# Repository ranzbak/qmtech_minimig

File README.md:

# Open Adaptive Amiga Retro System (Open AARS)

This PCB has been designed for my project in order to run the Minimig Amiga core on a board of my own design.
The core FPGA board I bought of Aliexpress, because soldering the very fine pitched BGA socket is too cumbersome.

More detailed documents regarding the I/O board can be found in the docs directory in this repository.

The board as is works, the features have been tested individually, but I'm still working on the Minimig port at this time.
Since I work on this in my spare time progress is not super fast, but progress is made.
For now I'm mostly learning and developing at the same time so a lot of stuff changes.
When the code base becomes more stable and usable I'll open the repository up.

[Firmware](https://github.com/ranzbak/MinimigAGA_TC64) for the Amiga works!

## Interfaces provided by this I/O board

- Atari/Amiga compatible Joystick ports
- PS/2 keyboard interface for mouse and keyboard
- Analog head phone jack via
- External floppy interface to connect Amiga floppy drives (Including 12V power pin)
- HDMI display connector that supports up to full HD video (1920x1080)
- 6 status LEDS
- Internal Amiga floppy drive connector
- External Amiga floppy drive connector (DIN-23)
- AS4C16M16SA-6TCN 32Mb SDRAM
- ADV7511 HDMI output PHY
- MAX9850 I2S Audio chip with built in amplifier
- SD-card interface
- RS-232 over USB to program and communicate with the Python shell

## Platforms that _could_ run with this IO board

- C64
- Amiga 1200/500(+) [https://github.com/ranzbak/MinimigAGA_TC64](https://github.com/ranzbak/MinimigAGA_TC64)
- Atari ST
- Other 80's and 90's machines?

Keep in mind I'm only planning on making an Amiga core for this board, but feel free to contribute other cores.

# The two boards that are compatible with this design are

## QM_XC7A100T_DDR3

### Specs

- On-Board FPGA: XC7A100T-2FGG676I;
- On-Board FPGA external crystal frequency: 50MHz;
- XC7A100T-2FGG676I has rich block RAM resource up to 4,860Kb;
- XC7A100T-2FGG676I has 101,440 logic cells;
- On-Board MT25QL128 SPI Flash,16M bytes for user configuration code;
- On-Board 256MB Micron DDR3，MT41K128M16JT-125:K;
- On-Board 3.3V power supply for FPGA by using MP2315 wide input range DC/DC;
- XC7A100T core board has two 64p, 2.54mm pitch headers for extending user IOs. All IOs are precisely designed with length matching;
- XC7A100T core board has 3 user switches;
- XC7A100T core board has 4 user LEDs;
- XC7A100T core board has JTAG interface, by using 6p, 2.54mm pitch header;
- XC7A100T core board PCB size is: 6.7cm x 8.4cm;
- Default power source for board is: 1A@5V DC, the DC header type: DC-050, 5.5mmx2.1mm;

### Github repo

[QM_XC7A100T_STARTER_KIT](https://github.com/ChinaQMTECH/QM_XC7A100T_STARTER_KIT)

### Listings at this time (2019-12-29)

- [Ebay QMTECH Xilinx FPGA Artix7 Artix-7 XC7A100T Core Board](https://www.ebay.com/itm/QMTECH-Xilinx-FPGA-Artix7-Artix-7-XC7A100T-Core-Board-/173922141347)
- [Aliexpress QMTECH Xilinx FPGA Artix7 Artix-7 XC7A100T DDR3 Core Board](vid=bcf629d3-8718-47b9-bad6-a31d7b1e778c&algo_expid=bcf629d3-8718-47b9-bad6-a31d7b1e778c-14&btsid=29203478-817f-4791-b6b6-1687369426ed&ws_ab_test=searchweb0_0,searchweb201602_3,searchweb201603_53)

## QM_XC7A35T_DDR3

### Specs

- On-Board FPGA: XC7A35T-1FTG256C;
- On-Board FPGA external crystal frequency: 50MHz;
- XC7A35T-1FTG256C has rich block RAM resource up to 1,800Kb;
- XC7A35T-1FTG256C has 33,280 logic cells;
- On-Board MT28QL128 SPI Flash, 16M bytes for user configuration code;
- On-Board 256MB Micron DDR3, MT41J128M16JT-125:K;
- On-Board 3.3V power supply for FPGA by using MP2315 wide input range DC/DC;
- XC7A35T development board has two 64p, 2.54mm pitch headers for extending user IOs. All IOs are precisely designed with length matching;
- XC7A35T development board has 2 user switches;
- XC7A35T development board has 3 user LEDs;
- XC7A35T development board has JTAG interface, by using 6p, 2.54mm pitch header;
- XC7A35T development board PCB size is: 6.7cm x 8.4cm;
- Default power source for board is: 1A@5V DC, the DC header type: DC-050, 5.5mmx2.1mm;

### Github repo

[QM_XC7A35T_DDR3](https://github.com/ChinaQMTECH/QM_XC7A35T_DDR3)

### Listings at this time (2019-12-29)

- [Ebay Xilinx FPGA Artix7 Artix-7 Core Board XC7A35T DDR3 256MB](https://www.ebay.com/itm/Xilinx-FPGA-Artix7-Artix-7-Core-Board-XC7A35T-DDR3-256MB/293211934785?hash=item4444cb1041:g:YGgAAOSw5SNdbdkY)
- [Aliexpress QMTECH Xilinx FPGA Artix7 Artix-7 Core Board XC7A35T DDR3 256MB](https://www.aliexpress.com/item/1000006630084.html?spm=a2g0o.productlist.0.0.41cd3b52ViiSyG&algo_pvid=42b95d99-f036-43b5-8cb0-6ca9003178e8&algo_expid=42b95d99-f036-43b5-8cb0-6ca9003178e8-3&btsid=62811540-f61c-4c9d-b4b2-447e53cca01b&ws_ab_test=searchweb0_0,searchweb201602_3,searchweb201603_53)

** Make sure to ask the seller to ship the board without the female headers soldered on, for the Open AARS board male headers are needed. **

## Disclaimer

THE PROJECT IS PROVIDED "AS IS", WITHOUT WARRANTY OF ANY KIND, EXPRESS OR IMPLIED, INCLUDING BUT NOT LIMITED TO THE WARRANTIES OF MERCHANTABILITY, FITNESS FOR A PARTICULAR PURPOSE AND NONINFRINGEMENT. IN NO EVENT SHALL THE AUTHORS OR COPYRIGHT HOLDERS BE LIABLE FOR ANY CLAIM, DAMAGES OR OTHER LIABILITY, WHETHER IN AN ACTION OF CONTRACT, TORT OR OTHERWISE, ARISING FROM, OUT OF OR IN CONNECTION WITH THE PROJECT OR THE USE OR OTHER DEALINGS IN THE PROJECT.

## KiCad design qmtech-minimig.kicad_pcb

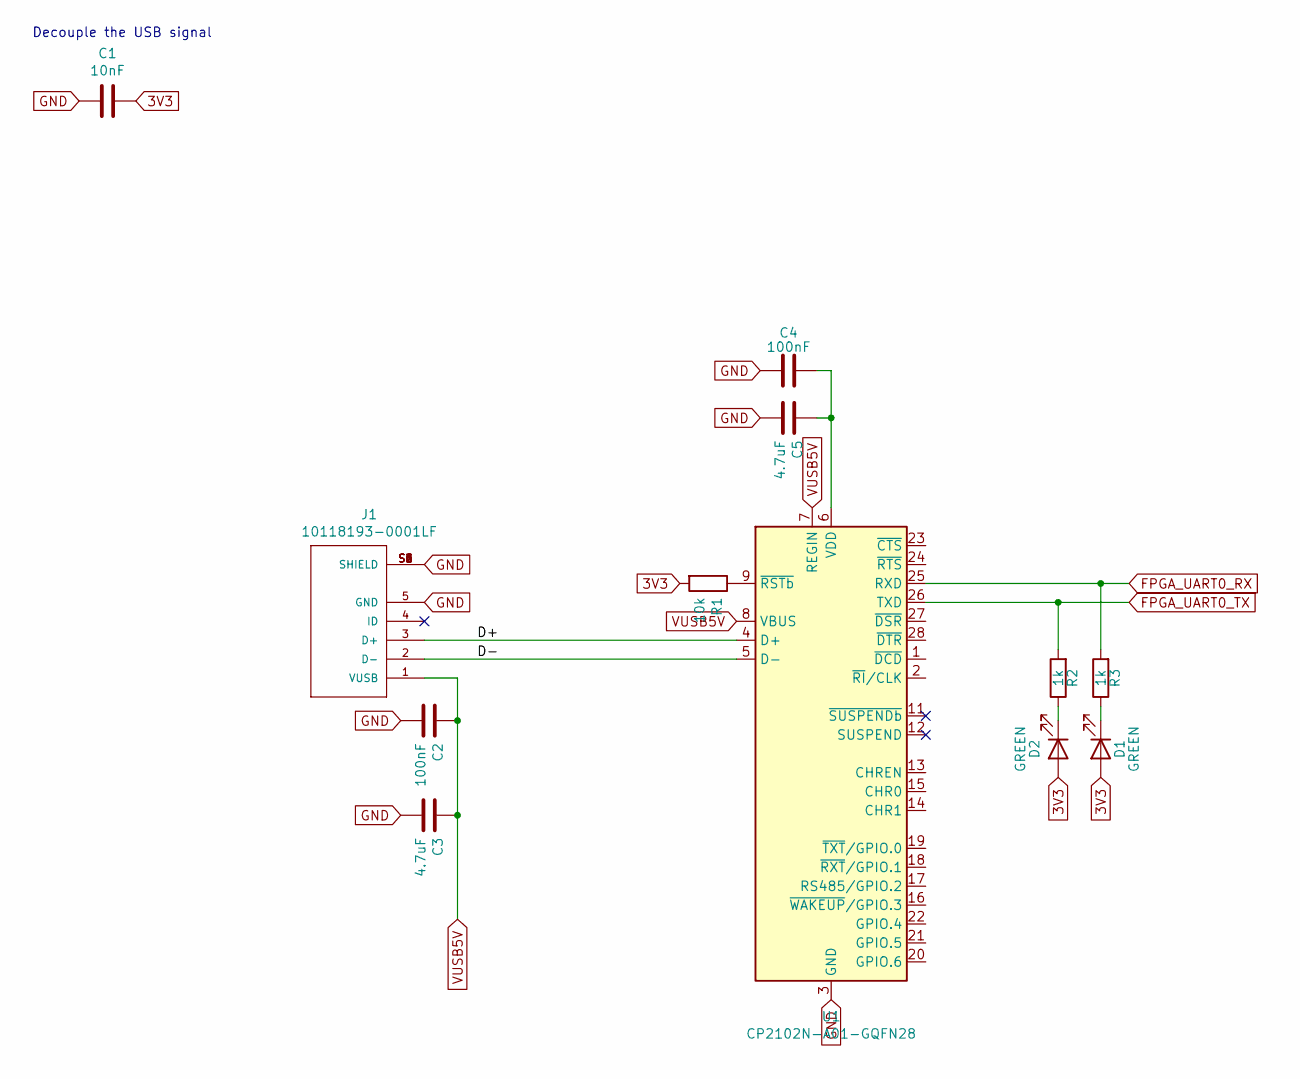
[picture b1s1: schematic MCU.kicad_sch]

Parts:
C1: 10nF; C_0603_1608Metric
C2, C4: 100nF; C_0603_1608Metric
C3, C5: 4.7uF; C_0805_2012Metric
D1, D2: GREEN; LED_0603_1608Metric
J1: 10118193-0001LF; FCI_10118193-0001LF
R1: 10k; R_0603_1608Metric
R2, R3: 1k; R_0603_1608Metric
U1: CP2102N-A01-GQFN28; QFN-28-1EP_5x5mm_P0.5mm_EP3.35x3.35mm

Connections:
3V3: C1.1, D1.2 (A), D2.2 (A), R1.2; also elsewhere on the board
/MCU/D+: J1.3 (D+), U1.4 (D+)
/MCU/D-: J1.2 (D-), U1.5 (D-)
FPGA_UART0_RX: R3.2, U1.25 (RXD); also elsewhere on the board
FPGA_UART0_TX: R2.2, U1.26 (TXD); also elsewhere on the board
unnamed: C4.2, C5.1, U1.6 (VDD)
unnamed: D1.1 (K), R2.1
unnamed: D2.1 (K), R3.1
unnamed: R1.1, U1.9 (~RSTb)
VUSB5V: C2.1, C3.1, J1.1 (VUSB), U1.7 (REGIN), U1.8 (VBUS)

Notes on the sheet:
Decouple the USB signal

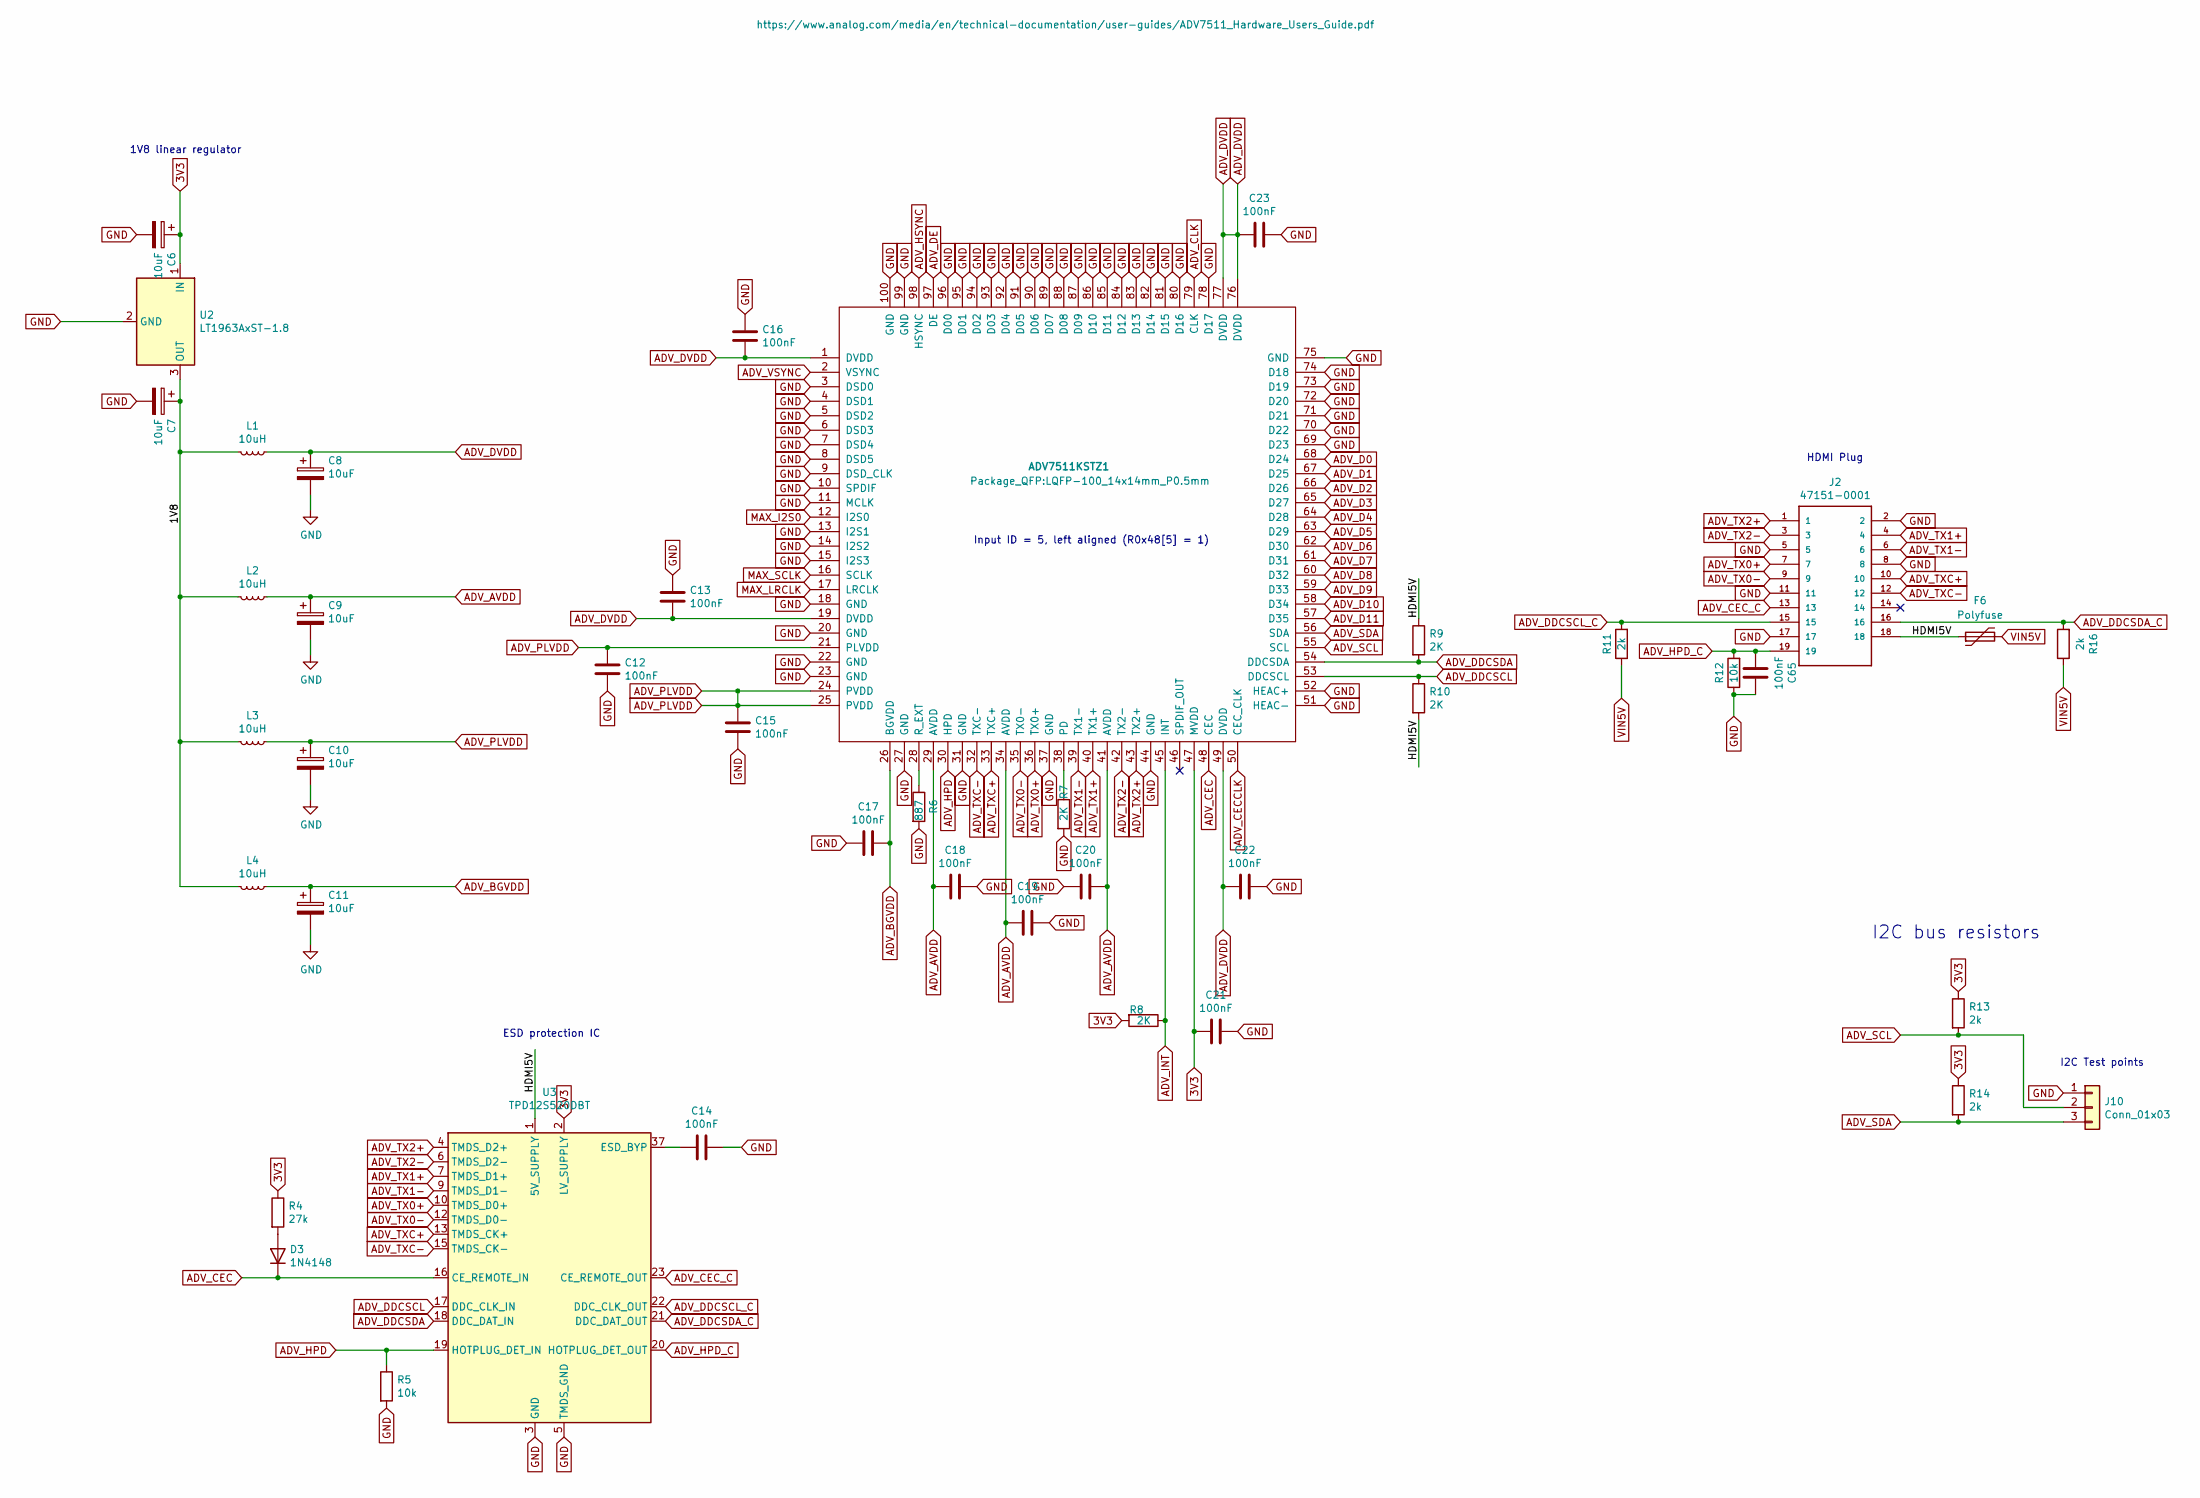
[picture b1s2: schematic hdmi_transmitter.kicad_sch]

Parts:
ADV7511KSTZ1: adv7511kstz; LQFP-100_14x14mm_P0.5mm
C6, C7, C8, C9, C10, C11: 10uF; C_0805_2012Metric
C12, C13, C14, C15, C16, C17, C18, C19, C20, C21, C22, C23, C65: 100nF; C_0603_1608Metric
D3: 1N4148; D_SOD-323
F6: Polyfuse; Fuse_0805_2012Metric
J2: 47151-0001
J10: Conn_01x03; PinHeader_1x03_P2.54mm_Vertical
L1, L2, L3, L4: 10uH; L_0805_2012Metric
R4: 27k; R_0603_1608Metric
R5, R12: 10k; R_0603_1608Metric
R6: 887; R_0603_1608Metric
R7, R8, R9, R10: 2K; R_0603_1608Metric
R11, R13, R14, R16: 2k; R_0603_1608Metric
U2: LT1963AxST-1.8; SOT-223-3_TabPin2
U3: TPD12S520DBT; TSSOP-38_4.4x9.7mm_P0.5mm

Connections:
3V3: ADV7511KSTZ1.47 (MVDD), C6.1, C21.2, R4.1, R8.2, R13.1, R14.1, U2.1 (IN), U3.2 (LV_SUPPLY); also elsewhere on the board
/HDMI transmitter/1V8: C7.1, L1.2, L2.2, L3.2, L4.2, U2.3 (OUT)
ADV_AVDD: ADV7511KSTZ1.29 (AVDD), ADV7511KSTZ1.34 (AVDD), ADV7511KSTZ1.41 (AVDD), C9.1, C18.2, C19.2, C20.1, L2.1
ADV_BGVDD: ADV7511KSTZ1.26 (BGVDD), C11.1, C17.1, L4.1
ADV_CEC: ADV7511KSTZ1.48 (CEC), D3.1 (K), U3.16 (CE_REMOTE_IN)
ADV_CECCLK: ADV7511KSTZ1.50 (CEC_CLK); also elsewhere on the board
ADV_CEC_C: J2.13, U3.23 (CE_REMOTE_OUT)
ADV_CLK: ADV7511KSTZ1.79 (CLK); also elsewhere on the board
ADV_D0: ADV7511KSTZ1.68 (D24); also elsewhere on the board
ADV_D1: ADV7511KSTZ1.67 (D25); also elsewhere on the board
ADV_D2: ADV7511KSTZ1.66 (D26); also elsewhere on the board
ADV_D3: ADV7511KSTZ1.65 (D27); also elsewhere on the board
ADV_D4: ADV7511KSTZ1.64 (D28); also elsewhere on the board
ADV_D5: ADV7511KSTZ1.63 (D29); also elsewhere on the board
ADV_D6: ADV7511KSTZ1.62 (D30); also elsewhere on the board
ADV_D7: ADV7511KSTZ1.61 (D31); also elsewhere on the board
ADV_D8: ADV7511KSTZ1.60 (D32); also elsewhere on the board
ADV_D9: ADV7511KSTZ1.59 (D33); also elsewhere on the board
ADV_D10: ADV7511KSTZ1.58 (D34); also elsewhere on the board
ADV_D11: ADV7511KSTZ1.57 (D35); also elsewhere on the board
ADV_DDCSCL: ADV7511KSTZ1.53 (DDCSCL), R10.1, U3.17 (DDC_CLK_IN)
ADV_DDCSCL_C: J2.15, R11.2, U3.22 (DDC_CLK_OUT)
ADV_DDCSDA: ADV7511KSTZ1.54 (DDCSDA), R9.2, U3.18 (DDC_DAT_IN)
ADV_DDCSDA_C: J2.16, R16.2, U3.21 (DDC_DAT_OUT)
ADV_DE: ADV7511KSTZ1.97 (DE); also elsewhere on the board
ADV_DVDD: ADV7511KSTZ1.1 (DVDD), ADV7511KSTZ1.19 (DVDD), ADV7511KSTZ1.49 (DVDD), ADV7511KSTZ1.76 (DVDD), ADV7511KSTZ1.77 (DVDD), C8.1, C13.1, C16.1, C22.2, C23.2, L1.1
ADV_HPD: ADV7511KSTZ1.30 (HPD), R5.1, U3.19 (HOTPLUG_DET_IN)
ADV_HPD_C: C65.2, J2.19, R12.2, U3.20 (HOTPLUG_DET_OUT)
ADV_HSYNC: ADV7511KSTZ1.98 (HSYNC); also elsewhere on the board
ADV_INT: ADV7511KSTZ1.45 (INT), R8.1; also elsewhere on the board
ADV_PLVDD: ADV7511KSTZ1.21 (PLVDD), ADV7511KSTZ1.24 (PVDD), ADV7511KSTZ1.25 (PVDD), C10.1, C12.2, C15.2, L3.1
ADV_SCL: ADV7511KSTZ1.55 (SCL), J10.2, R13.2; also elsewhere on the board
ADV_SDA: ADV7511KSTZ1.56 (SDA), J10.3, R14.2; also elsewhere on the board
ADV_TX0+: ADV7511KSTZ1.36 (TX0+), J2.7, U3.10 (TMDS_D0+), U3.29 (TMDS_D0+)
ADV_TX0-: ADV7511KSTZ1.35 (TX0-), J2.9, U3.12 (TMDS_D0-), U3.27 (TMDS_D0-)
ADV_TX1+: ADV7511KSTZ1.40 (TX1+), J2.4, U3.7 (TMDS_D1+), U3.32 (TMDS_D1+)
ADV_TX1-: ADV7511KSTZ1.39 (TX1-), J2.6, U3.9 (TMDS_D1-), U3.30 (TMDS_D1-)
ADV_TX2+: ADV7511KSTZ1.43 (TX2+), J2.1, U3.4 (TMDS_D2+), U3.35 (TMDS_D2+)
ADV_TX2-: ADV7511KSTZ1.42 (TX2-), J2.3, U3.6 (TMDS_D2-), U3.33 (TMDS_D2-)
ADV_TXC+: ADV7511KSTZ1.33 (TXC+), J2.10, U3.13 (TMDS_CK+), U3.26 (TMDS_CK+)
ADV_TXC-: ADV7511KSTZ1.32 (TXC-), J2.12, U3.15 (TMDS_CK-), U3.24 (TMDS_CK-)
ADV_VSYNC: ADV7511KSTZ1.2 (VSYNC); also elsewhere on the board
MAX_I2S0: ADV7511KSTZ1.12 (I2S0); also elsewhere on the board
MAX_LRCLK: ADV7511KSTZ1.17 (LRCLK); also elsewhere on the board
MAX_SCLK: ADV7511KSTZ1.16 (SCLK); also elsewhere on the board
unnamed: ADV7511KSTZ1.28 (R_EXT), R6.1
unnamed: ADV7511KSTZ1.38 (PD), R7.1
unnamed: C14.2, U3.37 (ESD_BYP)
unnamed: D3.2 (A), R4.2

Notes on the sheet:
1V8 linear regulator
HDMI Plug
Input ID = 5, left aligned (R0x48[5] = 1)
ESD protection IC
I2C Test points
I2C bus resistors

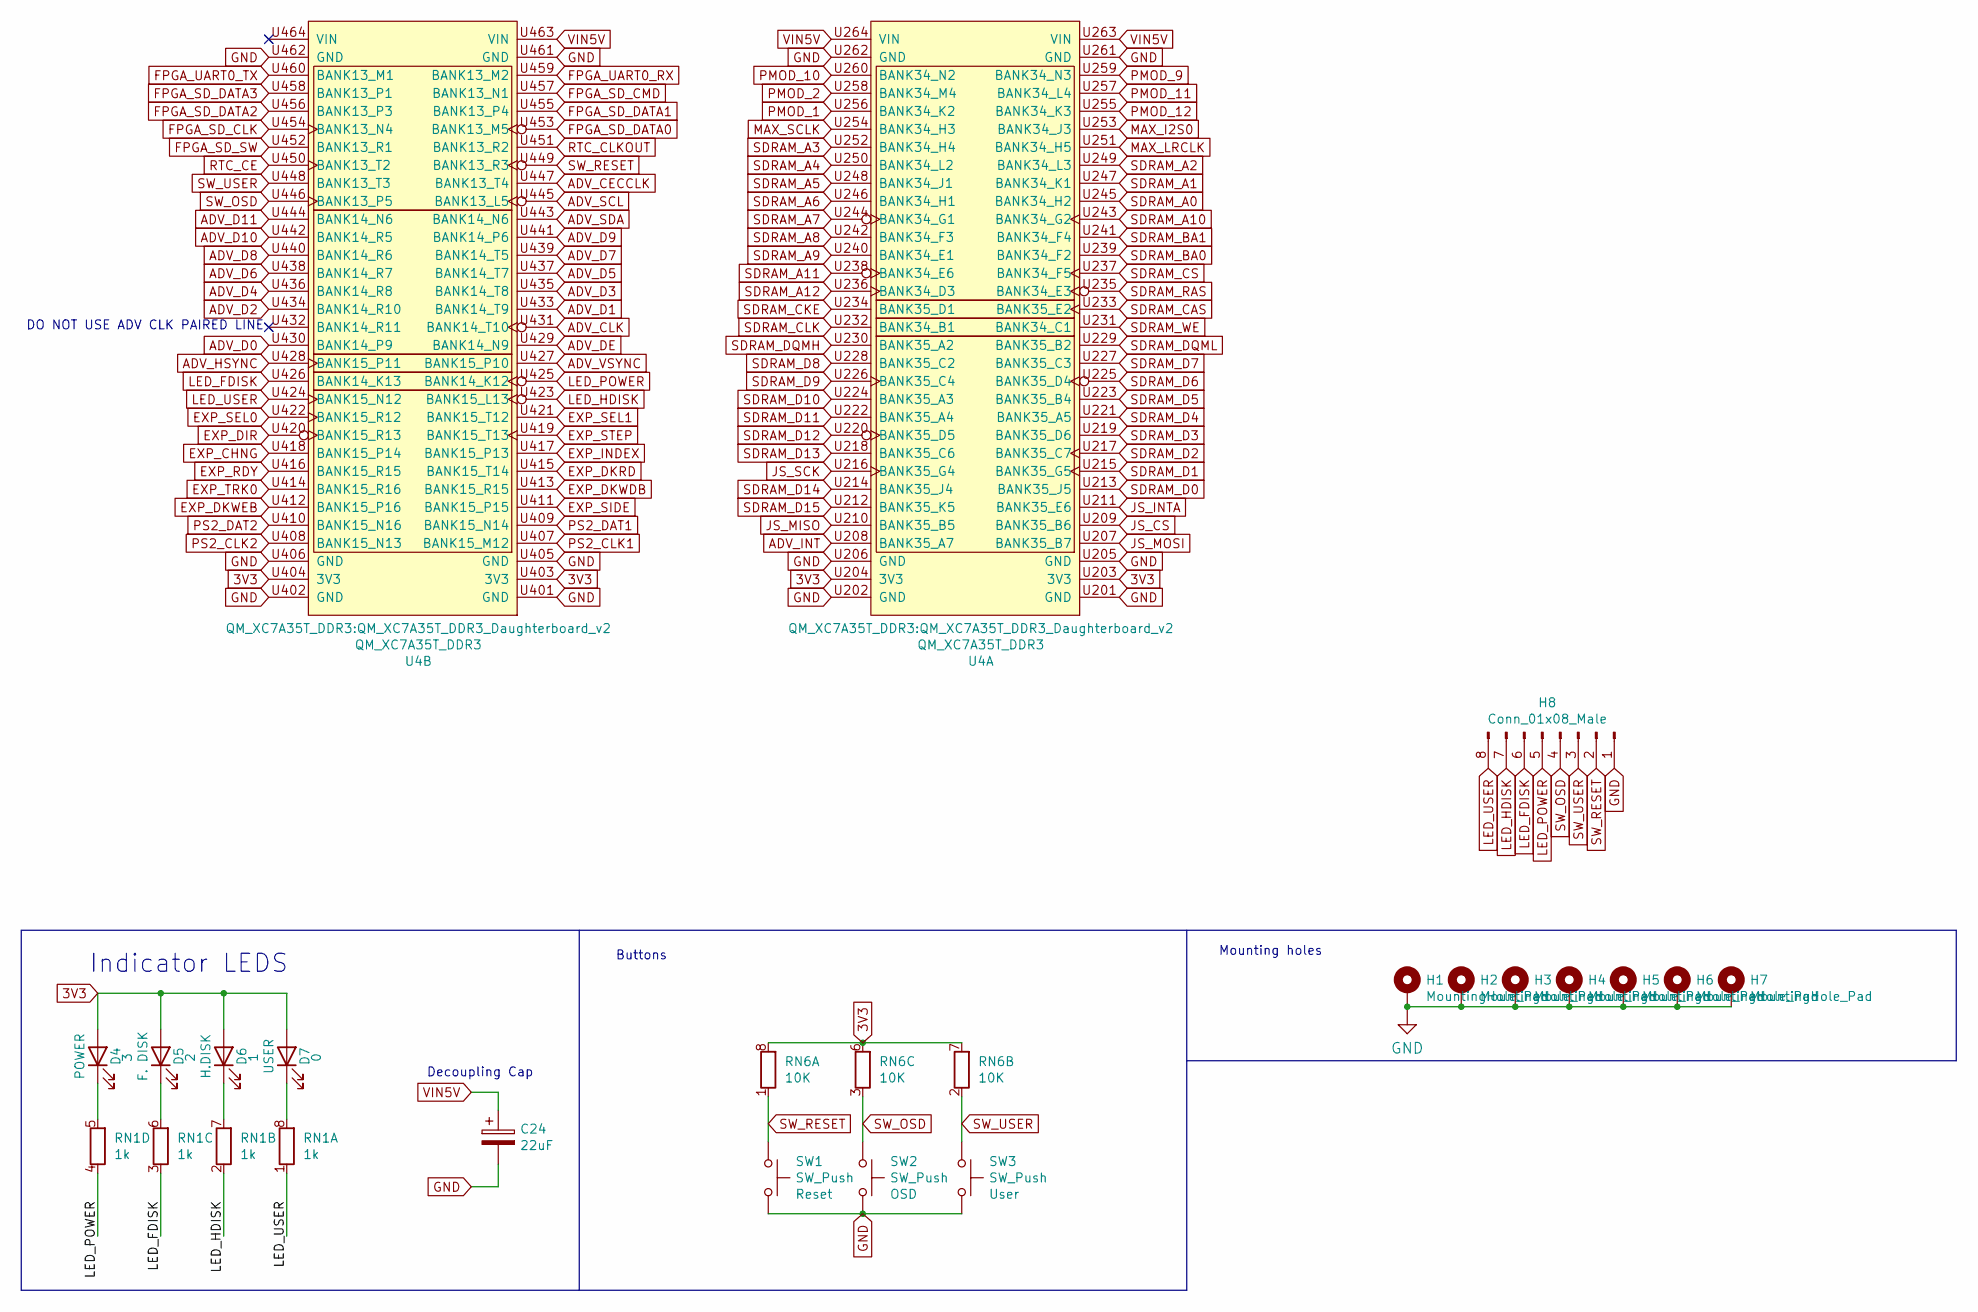
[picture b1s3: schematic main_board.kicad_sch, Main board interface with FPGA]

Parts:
C24: 22uF; CP_Elec_5x5.4
D4: 3; LED_0603_1608Metric
D5: 2; LED_0603_1608Metric
D6: 1; LED_0603_1608Metric
D7: 0; LED_0603_1608Metric
H1, H2, H3, H4, H5, H6, H7: MountingHole_Pad; MountingHole_3.2mm_M3_DIN965_Pad
H8: Conn_01x08_Male; PinHeader_1x08_P2.54mm_Vertical
RN1: 1k; R_Array_Convex_4x0603
RN6: 10K; R_Array_Concave_4x0603
SW1, SW2, SW3: SW_Push; SW_SPST_EVQQ2
U4: QM_XC7A35T_DDR3; QM_XC7A35T_DDR3_Daughterboard_v2

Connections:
3V3: D4.2 (A), D5.2 (A), D6.2 (A), D7.2 (A), RN6.6 (R3.2), RN6.7 (R2.2), RN6.8 (R1.2), U4.U203 (3V3), U4.U204 (3V3), U4.U403 (3V3), U4.U404 (3V3); also elsewhere on the board
ADV_CECCLK: U4.U447 (BANK13_T4); also elsewhere on the board
ADV_CLK: U4.U431 (BANK14_T10); also elsewhere on the board
ADV_D0: U4.U430 (BANK14_P9); also elsewhere on the board
ADV_D1: U4.U433 (BANK14_T9); also elsewhere on the board
ADV_D2: U4.U434 (BANK14_R10); also elsewhere on the board
ADV_D3: U4.U435 (BANK14_T8); also elsewhere on the board
ADV_D4: U4.U436 (BANK14_R8); also elsewhere on the board
ADV_D5: U4.U437 (BANK14_T7); also elsewhere on the board
ADV_D6: U4.U438 (BANK14_R7); also elsewhere on the board
ADV_D7: U4.U439 (BANK14_T5); also elsewhere on the board
ADV_D8: U4.U440 (BANK14_R6); also elsewhere on the board
ADV_D9: U4.U441 (BANK14_P6); also elsewhere on the board
ADV_D10: U4.U442 (BANK14_R5); also elsewhere on the board
ADV_D11: U4.U444 (BANK14_N6); also elsewhere on the board
ADV_DE: U4.U429 (BANK14_N9); also elsewhere on the board
ADV_HSYNC: U4.U428 (BANK15_P11); also elsewhere on the board
ADV_INT: U4.U208 (BANK35_A7); also elsewhere on the board
ADV_SCL: U4.U445 (BANK13_L5); also elsewhere on the board
ADV_SDA: U4.U443 (BANK14_N6); also elsewhere on the board
ADV_VSYNC: U4.U427 (BANK15_P10); also elsewhere on the board
EXP_CHNG: U4.U418 (BANK15_P14); also elsewhere on the board
EXP_DIR: U4.U420 (BANK15_R13); also elsewhere on the board
EXP_DKRD: U4.U415 (BANK15_T14); also elsewhere on the board
EXP_DKWDB: U4.U413 (BANK15_R15); also elsewhere on the board
EXP_DKWEB: U4.U412 (BANK15_P16); also elsewhere on the board
EXP_INDEX: U4.U417 (BANK15_P13); also elsewhere on the board
EXP_RDY: U4.U416 (BANK15_R15); also elsewhere on the board
EXP_SEL0: U4.U422 (BANK15_R12); also elsewhere on the board
EXP_SEL1: U4.U421 (BANK15_T12); also elsewhere on the board
EXP_SIDE: U4.U411 (BANK15_P15); also elsewhere on the board
EXP_STEP: U4.U419 (BANK15_T13); also elsewhere on the board
EXP_TRK0: U4.U414 (BANK15_R16); also elsewhere on the board
FPGA_SD_CLK: U4.U454 (BANK13_N4); also elsewhere on the board
FPGA_SD_CMD: U4.U457 (BANK13_N1); also elsewhere on the board
FPGA_SD_DATA0: U4.U453 (BANK13_M5); also elsewhere on the board
FPGA_SD_DATA1: U4.U455 (BANK13_P4); also elsewhere on the board
FPGA_SD_DATA2: U4.U456 (BANK13_P3); also elsewhere on the board
FPGA_SD_DATA3: U4.U458 (BANK13_P1); also elsewhere on the board
FPGA_UART0_RX: U4.U459 (BANK13_M2); also elsewhere on the board
FPGA_UART0_TX: U4.U460 (BANK13_M1); also elsewhere on the board
JS_CS: U4.U209 (BANK35_B6); also elsewhere on the board
JS_INTA: U4.U211 (BANK35_E6); also elsewhere on the board
JS_MISO: U4.U210 (BANK35_B5); also elsewhere on the board
JS_MOSI: U4.U207 (BANK35_B7); also elsewhere on the board
JS_SCK: U4.U216 (BANK35_G4); also elsewhere on the board
LED_FDISK: H8.6, RN1.3 (R3.1), U4.U426 (BANK14_K13)
LED_HDISK: H8.7, RN1.2 (R2.1), U4.U423 (BANK15_L13)
LED_POWER: H8.5, RN1.4 (R4.1), U4.U425 (BANK14_K12)
LED_USER: H8.8, RN1.1 (R1.1), U4.U424 (BANK15_N12)
MAX_I2S0: U4.U253 (BANK34_J3); also elsewhere on the board
MAX_LRCLK: U4.U251 (BANK34_H5); also elsewhere on the board
MAX_SCLK: U4.U254 (BANK34_H3); also elsewhere on the board
unnamed: D4.1 (K), RN1.5 (R4.2)
unnamed: D5.1 (K), RN1.6 (R3.2)
unnamed: D6.1 (K), RN1.7 (R2.2)
unnamed: D7.1 (K), RN1.8 (R1.2)
PMOD_1: U4.U256 (BANK34_K2); also elsewhere on the board
PMOD_2: U4.U258 (BANK34_M4); also elsewhere on the board
PMOD_9: U4.U259 (BANK34_N3); also elsewhere on the board
PMOD_10: U4.U260 (BANK34_N2); also elsewhere on the board
PMOD_11: U4.U257 (BANK34_L4); also elsewhere on the board
PMOD_12: U4.U255 (BANK34_K3); also elsewhere on the board
PS2_CLK1: U4.U407 (BANK15_M12); also elsewhere on the board
PS2_CLK2: U4.U408 (BANK15_N13); also elsewhere on the board
PS2_DAT1: U4.U409 (BANK15_N14); also elsewhere on the board
PS2_DAT2: U4.U410 (BANK15_N16); also elsewhere on the board
SDRAM_A0: U4.U245 (BANK34_H2); also elsewhere on the board
SDRAM_A1: U4.U247 (BANK34_K1); also elsewhere on the board
SDRAM_A2: U4.U249 (BANK34_L3); also elsewhere on the board
SDRAM_A3: U4.U252 (BANK34_H4); also elsewhere on the board
SDRAM_A4: U4.U250 (BANK34_L2); also elsewhere on the board
SDRAM_A5: U4.U248 (BANK34_J1); also elsewhere on the board
SDRAM_A6: U4.U246 (BANK34_H1); also elsewhere on the board
SDRAM_A7: U4.U244 (BANK34_G1); also elsewhere on the board
SDRAM_A8: U4.U242 (BANK34_F3); also elsewhere on the board
SDRAM_A9: U4.U240 (BANK34_E1); also elsewhere on the board
SDRAM_A10: U4.U243 (BANK34_G2); also elsewhere on the board
SDRAM_A11: U4.U238 (BANK34_E6); also elsewhere on the board
SDRAM_A12: U4.U236 (BANK34_D3); also elsewhere on the board
SDRAM_BA0: U4.U239 (BANK34_F2); also elsewhere on the board
SDRAM_BA1: U4.U241 (BANK34_F4); also elsewhere on the board
SDRAM_CAS: U4.U233 (BANK35_E2); also elsewhere on the board
SDRAM_CKE: U4.U234 (BANK35_D1); also elsewhere on the board
SDRAM_CLK: U4.U232 (BANK34_B1); also elsewhere on the board
SDRAM_CS: U4.U237 (BANK34_F5); also elsewhere on the board
SDRAM_D0: U4.U213 (BANK35_J5); also elsewhere on the board
SDRAM_D1: U4.U215 (BANK35_G5); also elsewhere on the board
SDRAM_D2: U4.U217 (BANK35_C7); also elsewhere on the board
SDRAM_D3: U4.U219 (BANK35_D6); also elsewhere on the board
SDRAM_D4: U4.U221 (BANK35_A5); also elsewhere on the board
SDRAM_D5: U4.U223 (BANK35_B4); also elsewhere on the board
SDRAM_D6: U4.U225 (BANK35_D4); also elsewhere on the board
SDRAM_D7: U4.U227 (BANK35_C3); also elsewhere on the board
SDRAM_D8: U4.U228 (BANK35_C2); also elsewhere on the board
SDRAM_D9: U4.U226 (BANK35_C4); also elsewhere on the board
SDRAM_D10: U4.U224 (BANK35_A3); also elsewhere on the board
SDRAM_D11: U4.U222 (BANK35_A4); also elsewhere on the board
SDRAM_D12: U4.U220 (BANK35_D5); also elsewhere on the board
SDRAM_D13: U4.U218 (BANK35_C6); also elsewhere on the board
SDRAM_D14: U4.U214 (BANK35_J4); also elsewhere on the board
SDRAM_D15: U4.U212 (BANK35_K5); also elsewhere on the board
SDRAM_DQMH: U4.U230 (BANK35_A2); also elsewhere on the board
SDRAM_DQML: U4.U229 (BANK35_B2); also elsewhere on the board
SDRAM_RAS: U4.U235 (BANK34_E3); also elsewhere on the board
SDRAM_WE: U4.U231 (BANK34_C1); also elsewhere on the board
VIN5V: C24.1, U4.U263 (VIN), U4.U264 (VIN), U4.U463 (VIN); also elsewhere on the board

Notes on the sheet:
DO NOT USE ADV CLK PAIRED LINE
Buttons
Decoupling Cap
Mounting holes
Indicator LEDS

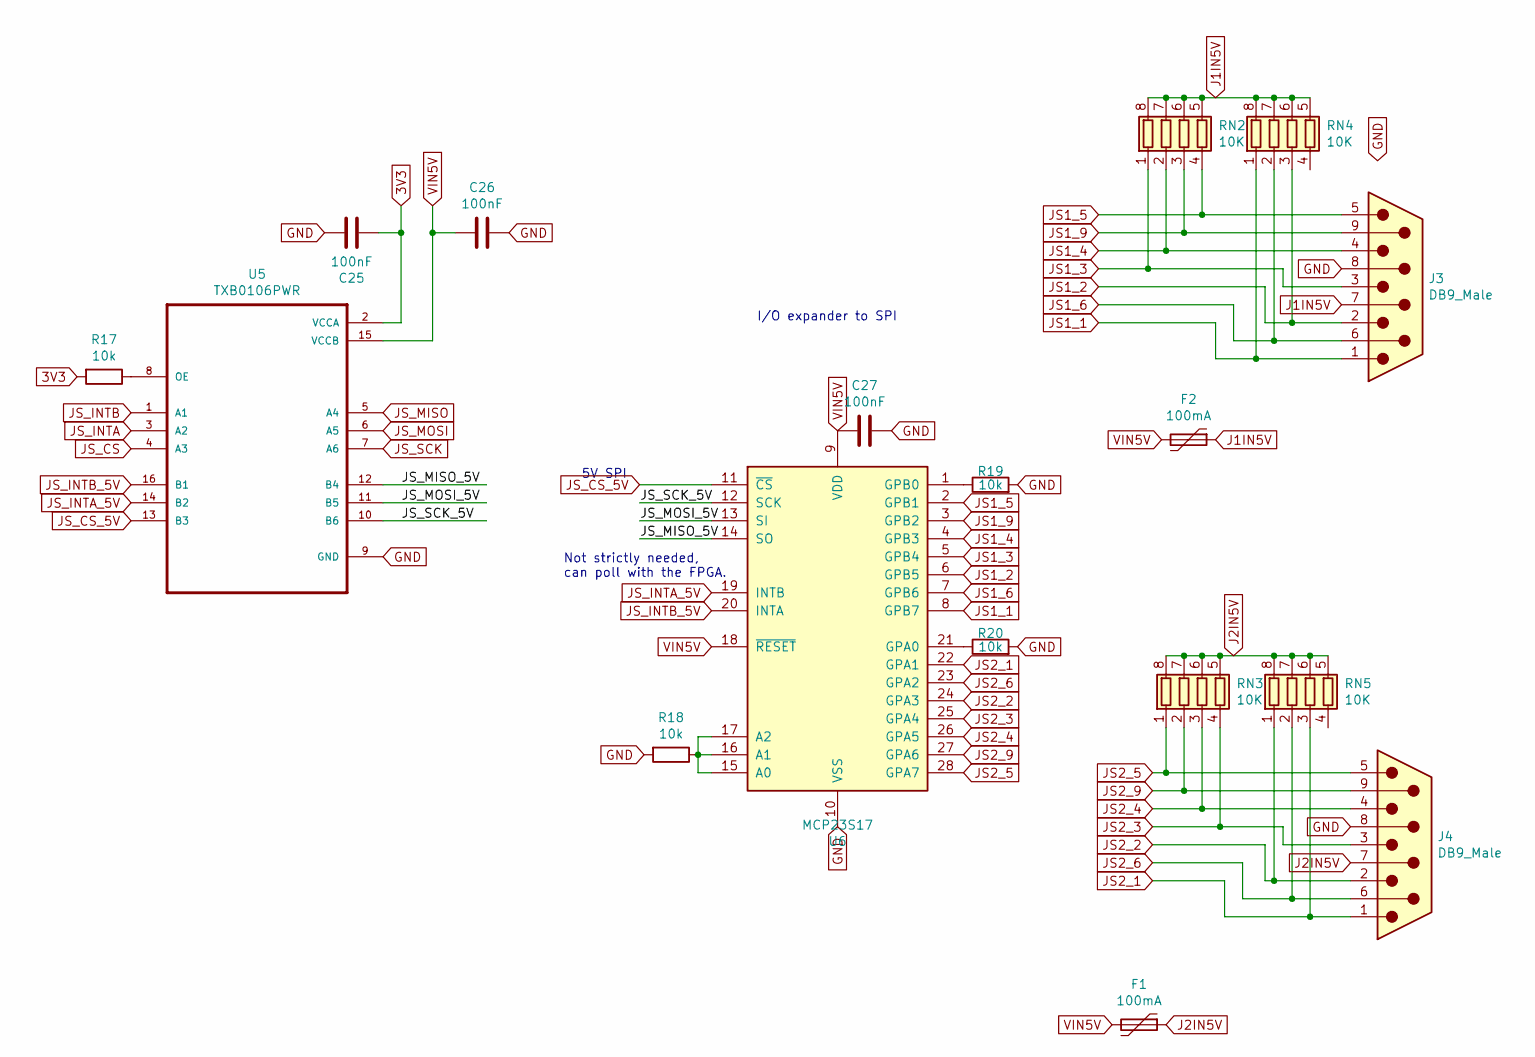
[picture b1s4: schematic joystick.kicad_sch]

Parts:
C25, C26, C27: 100nF; C_0603_1608Metric
F1, F2: 100mA; Fuse_0805_2012Metric
J3, J4: DB9_Male; DSUB-9_Male_Horizontal_P2.77x2.84mm_EdgePinOffset7.70mm_Hou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
R17, R18, R19, R20: 10k; R_0603_1608Metric
RN2, RN3, RN4, RN5: 10K; R_Array_Convex_4x0603
U5: TXB0106PWR; SOP65P640X120-16N
U6: MCP23S17; SSOP-28_5.3x10.2mm_P0.65mm

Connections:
3V3: C25.2, R17.2, U5.2 (VCCA); also elsewhere on the board
/Joystick/JS_MISO_5V: U5.12 (B4), U6.14 (SO)
/Joystick/JS_MOSI_5V: U5.11 (B5), U6.13 (SI)
/Joystick/JS_SCK_5V: U5.10 (B6), U6.12 (SCK)
J1IN5V: F2.1, J3.7, RN2.5 (R4.2), RN2.6 (R3.2), RN2.7 (R2.2), RN2.8 (R1.2), RN4.5 (R4.2), RN4.6 (R3.2), RN4.7 (R2.2), RN4.8 (R1.2)
J2IN5V: F1.1, J4.7, RN3.5 (R4.2), RN3.6 (R3.2), RN3.7 (R2.2), RN3.8 (R1.2), RN5.5 (R4.2), RN5.6 (R3.2), RN5.7 (R2.2), RN5.8 (R1.2)
JS1_1: J3.1, RN4.1 (R1.1), U6.8 (GPB7)
JS1_2: J3.2, RN4.3 (R3.1), U6.6 (GPB5)
JS1_3: J3.3, RN2.1 (R1.1), U6.5 (GPB4)
JS1_4: J3.4, RN2.2 (R2.1), U6.4 (GPB3)
JS1_5: J3.5, RN2.4 (R4.1), U6.2 (GPB1)
JS1_6: J3.6, RN4.2 (R2.1), U6.7 (GPB6)
JS1_9: J3.9, RN2.3 (R3.1), U6.3 (GPB2)
JS2_1: J4.1, RN5.3 (R3.1), U6.22 (GPA1)
JS2_2: J4.2, RN5.1 (R1.1), U6.24 (GPA3)
JS2_3: J4.3, RN3.4 (R4.1), U6.25 (GPA4)
JS2_4: J4.4, RN3.3 (R3.1), U6.26 (GPA5)
JS2_5: J4.5, RN3.1 (R1.1), U6.28 (GPA7)
JS2_6: J4.6, RN5.2 (R2.1), U6.23 (GPA2)
JS2_9: J4.9, RN3.2 (R2.1), U6.27 (GPA6)
JS_CS: U5.4 (A3); also elsewhere on the board
JS_CS_5V: U5.13 (B3), U6.11 (~CS)
JS_INTA: U5.3 (A2); also elsewhere on the board
JS_INTA_5V: U5.14 (B2), U6.19 (INTB)
JS_INTB: U5.1 (A1)
JS_INTB_5V: U5.16 (B1), U6.20 (INTA)
JS_MISO: U5.5 (A4); also elsewhere on the board
JS_MOSI: U5.6 (A5); also elsewhere on the board
JS_SCK: U5.7 (A6); also elsewhere on the board
unnamed: R17.1, U5.8 (OE)
unnamed: R18.1, U6.15 (A0), U6.16 (A1), U6.17 (A2)
unnamed: R19.1, U6.1 (GPB0)
unnamed: R20.1, U6.21 (GPA0)
VIN5V: C26.2, C27.2, F1.2, F2.2, U5.15 (VCCB), U6.9 (VDD), U6.18 (~RESET); also elsewhere on the board

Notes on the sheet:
Not strictly needed, can poll with the FPGA.
I/O expander to SPI
5V SPI

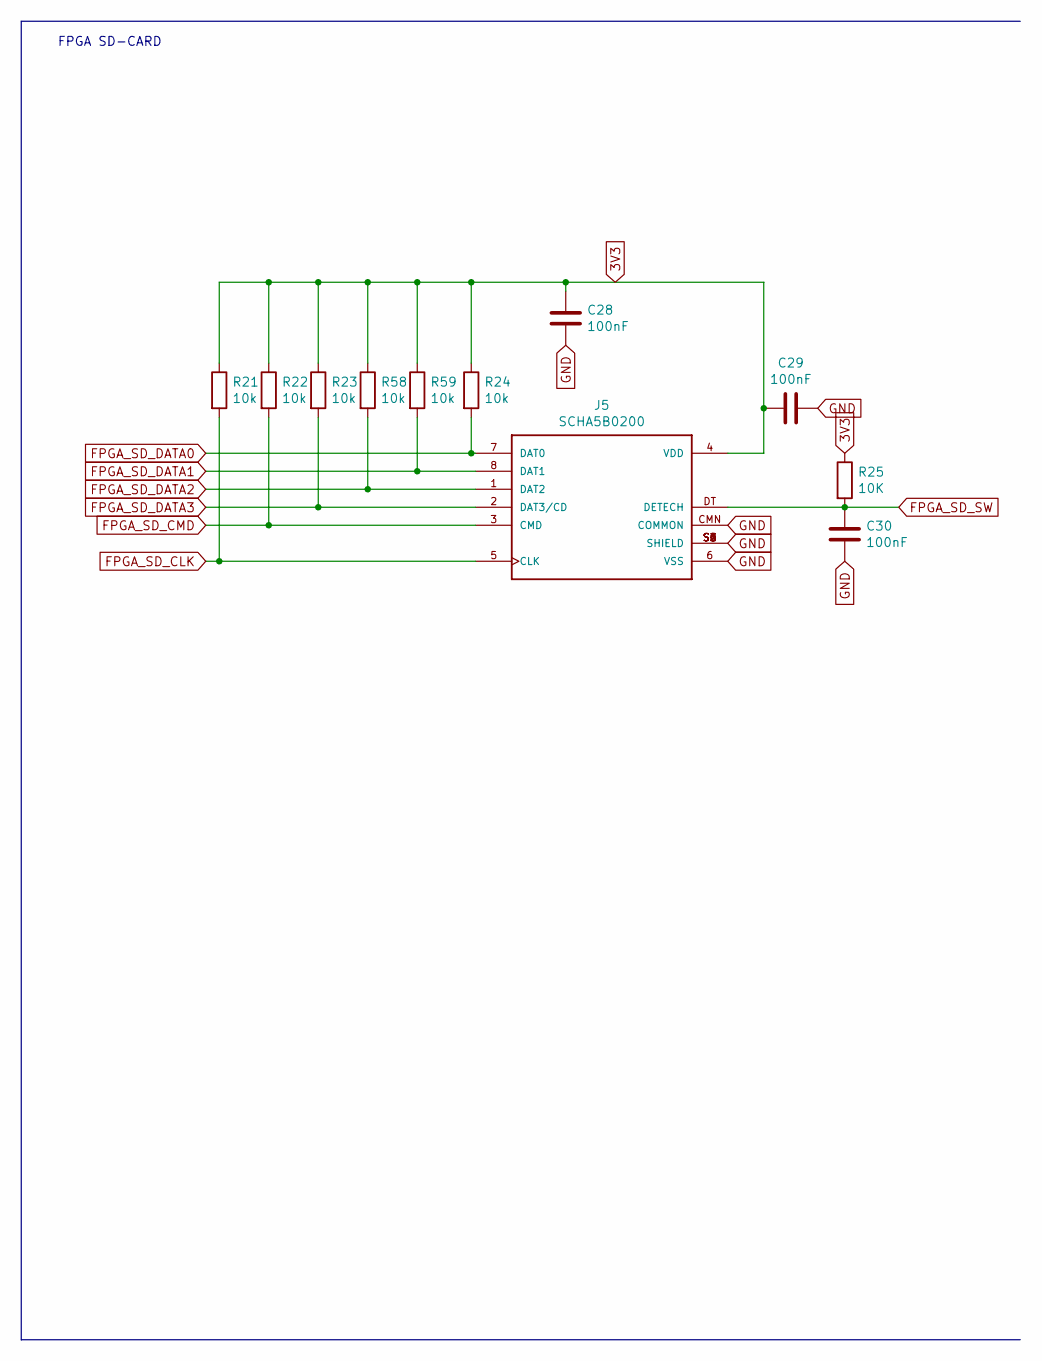
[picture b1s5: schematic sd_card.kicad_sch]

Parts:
C28, C29, C30: 100nF; C_0603_1608Metric
J5: SCHA5B0200; ALPS_SCHA5B0200
R21, R22, R23, R24, R58, R59: 10k; R_0603_1608Metric
R25: 10K; R_0603_1608Metric

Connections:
3V3: C28.1, C29.2, J5.4 (VDD), R21.1, R22.1, R23.1, R24.1, R25.1, R58.1, R59.1; also elsewhere on the board
FPGA_SD_CLK: J5.5 (CLK), R21.2; also elsewhere on the board
FPGA_SD_CMD: J5.3 (CMD), R22.2; also elsewhere on the board
FPGA_SD_DATA0: J5.7 (DAT0), R24.2; also elsewhere on the board
FPGA_SD_DATA1: J5.8 (DAT1), R59.2; also elsewhere on the board
FPGA_SD_DATA2: J5.1 (DAT2), R58.2; also elsewhere on the board
FPGA_SD_DATA3: J5.2 (DAT3/CD), R23.2; also elsewhere on the board

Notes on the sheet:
FPGA SD-CARD

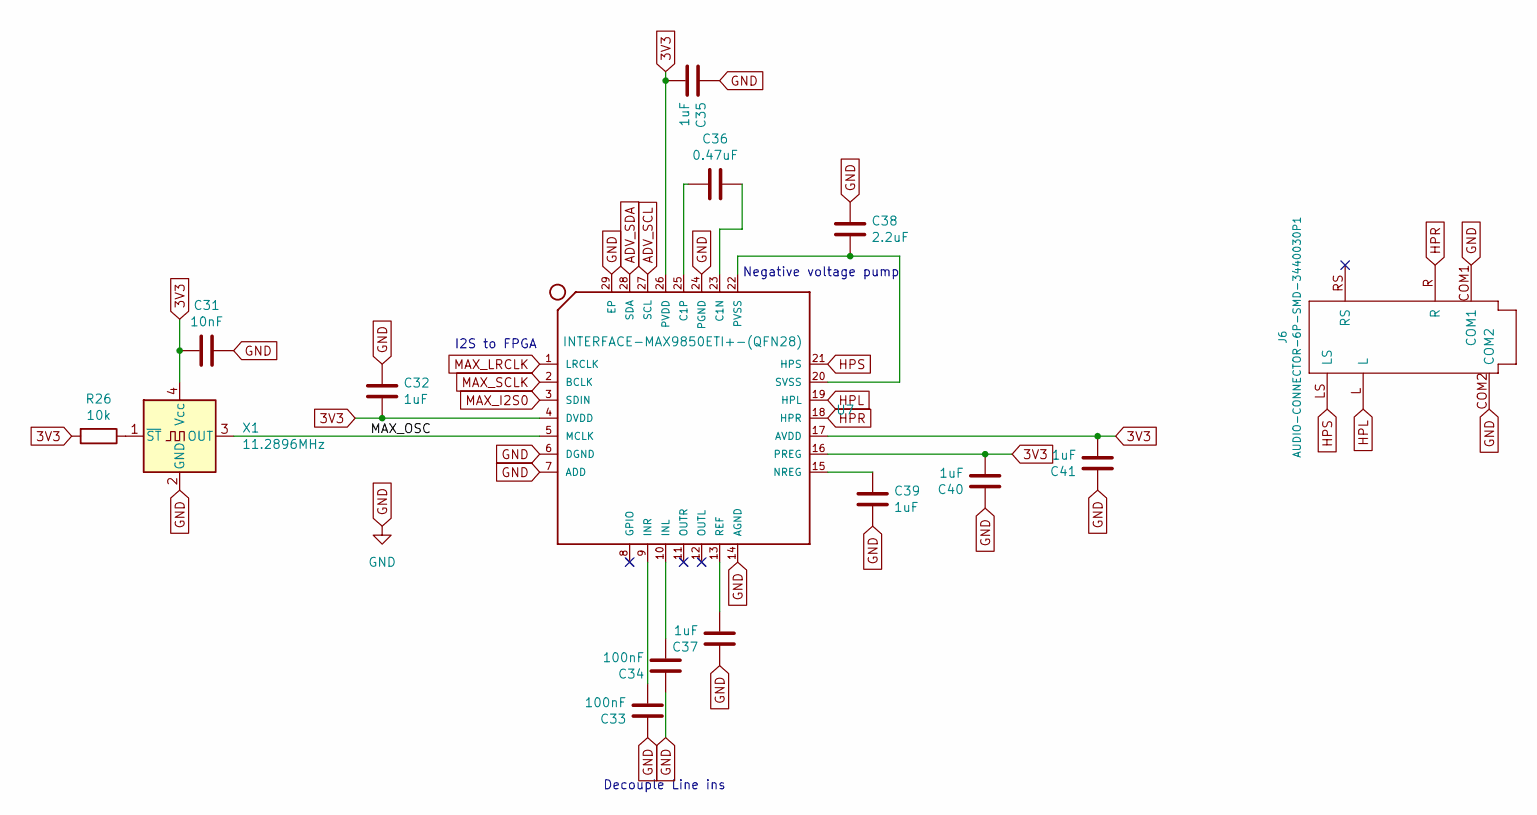
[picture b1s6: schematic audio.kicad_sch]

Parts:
C31: 10nF; C_0603_1608Metric
C32, C35, C37, C39, C40, C41: 1uF; C_0603_1608Metric
C33, C34: 100nF; C_0603_1608Metric
C36: 0.47uF; C_0603_1608Metric
C38: 2.2uF; C_0805_2012Metric
J6: AUDIO-CONNECTOR-6P-SMD-3440030P1; 6P-SMD-3.5
R26: 10k; R_0603_1608Metric
U7: INTERFACE-MAX9850ETI+-(QFN28); QFN28G_0.5-5X5MM
X1: 11.2896MHz; Oscillator_SMD_SeikoEpson_SG210-4Pin_2.5x2.0mm

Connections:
3V3: C31.1, C32.2, C35.2, C40.2, C41.2, R26.2, U7.4 (DVDD), U7.16 (PREG), U7.17 (AVDD), U7.26 (PVDD), X1.4 (Vcc); also elsewhere on the board
/Audio/MAX_OSC: U7.5 (MCLK), X1.3 (OUT)
ADV_SCL: U7.27 (SCL); also elsewhere on the board
ADV_SDA: U7.28 (SDA); also elsewhere on the board
HPL: J6.L, U7.19 (HPL)
HPR: J6.R, U7.18 (HPR)
HPS: J6.LS, U7.21 (HPS)
MAX_I2S0: U7.3 (SDIN); also elsewhere on the board
MAX_LRCLK: U7.1 (LRCLK); also elsewhere on the board
MAX_SCLK: U7.2 (BCLK); also elsewhere on the board
unnamed: C33.2, U7.9 (INR)
unnamed: C34.2, U7.10 (INL)
unnamed: C36.1, U7.23 (C1N)
unnamed: C36.2, U7.25 (C1P)
unnamed: C37.2, U7.13 (REF)
unnamed: C38.2, U7.20 (SVSS), U7.22 (PVSS)
unnamed: C39.1, U7.15 (NREG)
unnamed: R26.1, X1.1 (~ST)

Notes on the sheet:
Decouple Line ins
Negative voltage pump
I2S to FPGA

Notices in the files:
qmtech-minimig.kicad_pcb:
CERN Open Hardware Licence
